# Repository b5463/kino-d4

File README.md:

<div align="center">
  <picture>
    <source media="(prefers-color-scheme: dark)" srcset="docs/assets/brand/kino-d4-white-on-dark.png">
    
  </picture>

  <h3>Four cameras. One button. One moving photograph.</h3>

  <p>

  </p>

  <p>
    <a href="#try-studio">Try Studio</a> ·
    <a href="docs/HARDWARE.md">Hardware</a> ·
    <a href="firmware-contract/README.md">Firmware contract</a> ·
    <a href="https://github.com/users/b5463/projects/3">Project</a> ·
    <a href="docs/DEVELOPMENT.md">Build notes</a> ·
    <a href="docs/VERSIONING.md">Versions</a>
  </p>
</div>

KINO D4 is a handmade four-lens camera built for house parties. Press the shutter and four cameras fire from slightly different positions. The result can stay as four photographs or become a short, looping wiggle with real parallax.

Direct flash. 4:3 frames. Originals saved first. No cloud anywhere near the shutter.

<p align="center"><sub>The actual Studio overview, connected to KINO Twin — the simulated camera that ships in this repository.</sub></p>

## Why this repository exists

A five-controller camera is miserable to service with an IDE, five serial logs, and hand-edited JSON. KINO Studio puts the whole machine behind one USB cable: all four sensors, power, storage, recipes, calibration, firmware, logs, and recovery.

The repository contains that workbench, the wire protocol it speaks, the Roll backend used after capture, shared document schemas, and a reference camera that can fail on command.

> **Honest build status.** The software works against the simulated camera and is covered by tests that need no hardware. That is Studio, the protocol, the Roll backend and its workers, the guest client, and KINO Twin.
>
> There is a real camera now. Firmware 0.4.55 captures on all four cameras and writes the originals to the card. It draws its own screens. Since 0.4.4 it has uploaded to a Roll over Wi-Fi from the body itself. The body is released too: design 0.1.4, a printable PETG slab, measured rather than estimated.
>
> Three things are not finished, and it is worth naming them here rather than leaving a reader to find out.
>
> The camera has **no flash**. [`ECN-0003`](hardware/changes/ECN-0003-shutter-on-jp1-21.md) dropped the assembly and gave its enable pin to the shutter. A replacement module has not been chosen.
>
> **Exposure skew between the four cameras has never been measured.** That is the number the wiggle's quality actually rests on. Firmware reports the two skews it can observe and returns `null` for this one, with a reason.
>
> **There is no public front door yet.** The operator's line sits behind O2 carrier NAT, so `kino.acronym.sk` cannot point at the PC, and no ingress has been selected — see [the standing decision](docs/runbooks/public-ingress-options.md#standing-decision-2026-09-09). A party still works: the camera writes to its card first and uploads when it can.

## Try Studio

You need Node.js 22 or newer.

```bash
npm ci
npm run build -w @kino/studio -w @kino/twin
npm run preview:all
```

Open <http://localhost:4400/studio/>, then open <http://localhost:4400/dev/twin/> in a second tab and press **CONNECT KINO TWIN** back in Studio. KINO Twin is the simulated camera: it speaks the same protocol as hardware, so Studio exercises its full interface without a D4 on the bench.

Both apps must be served from one origin, as `preview:all` does — the bridge between them is a `BroadcastChannel`. To run them on separate dev servers instead, start `npm run twin:relay` and open Twin with `?ws=1`; Studio offers the bridge automatically in a dev build.

A physical D4 needs desktop Chrome or Edge for Web Serial.

Run the checks:

```bash
npm run lint
npm run test -w @kino/studio -w @kino/kdp -w @kino/schemas -w @kino/test-fixtures -w @kino/hardware-profiles -w @kino/simulator-engine -w @kino/three-assets -w @kino/twin -w @kino/design-system -w @kino/media -w @kino/roll-web
npm run build
```

That is every JavaScript suite that runs without Docker, and the same line CI runs. The API and worker also need PostgreSQL, Redis, and S3-compatible storage; their local stack and ports are documented in [the development guide](docs/DEVELOPMENT.md#api-stack).

Two suites are outside that line on purpose. The firmware's are C, built and run with `make -C firmware/p4/host_tests test-all` and `make -C firmware/components/kdp_core/host_tests` — 6,246 checks that need no camera, and the two that link cJSON need the IDF container. KINO Print's are Python (`npm run test -w @kino/print`), so a bare `npm test` at the root fails on a machine without Python.

## The three tools

Every screen below is a capture of the running application against the included simulator. No hardware was attached.

### KINO Studio

The workbench behind one USB cable: all four sensors, power, storage, recipes, calibration, firmware, logs, and recovery. Shown at the top of this page connected to KINO Twin.

### KINO Twin

A working 3D copy of the D4. It speaks the same KDP as real hardware: power it on, fire the shutter, watch the display, click any part for its dimensions and clearances. Measurement findings gate the enclosure lock.

<p align="center"><sub>KINO Twin, simulator powered on. Everything shown is simulated and labelled as such.</sub></p>

### KINO Roll

The shared album after the party. The camera uploads over Wi-Fi; guests open a link, watch photos arrive live, view the four frames behind each one, favourite and download. The client is a PWA that works on a phone at the event.

The host gets a separate surface on the same link: a dashboard that says which camera is uploading and which is stuck, hides or restores a photograph, clears the roll, and exports the lot as a ZIP. A roll can carry a PIN, and a trashed photograph stays recoverable for seven days. There is a third surface for a screen at the party — a projector page that cycles the newest captures and keeps the display awake.

The Roll is run for an event rather than hosted permanently: the origin is a laptop, reached through an outbound tunnel for the night, with no port forwarded. [`docs/runbooks/event-day.md`](docs/runbooks/event-day.md) is the procedure, and it ends by taking the tunnel down.

<p align="center"><sub>The guest gallery with demo captures from the test uploader.</sub></p>

<p align="center"><sub>One photo: the D4 frame strip switches the preview. Simulated captures.</sub></p>

### And one workshop tool

[KINO Print](apps/prusa-print-98/README.md) is not part of the camera. It is a local print host for the MK3S that prints the body, and it is here because the bodies in this repository kept failing on the bed for reasons a slicer does not warn about. It reads the PrusaSlicer metadata out of a `.gcode`, refuses to start until a person confirms the printer is physically clear, and streams the job itself. Its PETG preflight is the point: it catches a first layer that is too hot, full-temperature probing, a profile mismatch, and a nozzle that heats before the bed wait, then holds the nozzle at 170 °C through bed heating and mesh levelling and raises it just before the prime line. The source file is never modified.

## What comes out of the camera

### WIGGLE

Four matched frames play `1 → 2 → 3 → 4 → 3 → 2`. Nothing is synthesized between them. The movement comes from the four real viewpoints.

### QUAD

Each camera can use a different recipe on the same shutter press. A single capture might produce PARTY NEG, MOTION, RAW DIGI, and ACROS-ISH together.

Both modes obey the same boring, important rule: the microSD card gets the originals before anything is rendered, uploaded, cropped, or shared. Derivatives are disposable. Originals are not.

## The camera

| Part | D4 V1 hardware |
|---|---|
| Main unit | Guition JC4880P443C-I-W, ESP32-P4 + ESP32-C6, 4.3-inch 480 × 800 touch display |
| Camera row | 4 × Seeed XIAO ESP32-S3 Sense |
| Sensors | 4 × OV3660 rolling-shutter sensors, up to 2048 × 1536 |
| Storage | 32 GB microSD |
| Battery | 1S 3000 mAh LiPo |
| Flash | **Not fitted.** `ECN-0003` dropped the direct-flash assembly and gave its enable pin to the shutter; an external module will replace it and is not chosen |
| Sound | 8 Ω / 2 W speaker |
| Camera wiring | Four UART pairs plus one shared sync line |
| Body | Printed PETG slab, 131 × 90 × 65.5 mm, design 0.1.4 — two-part chassis, glued face shell, sliding lens cover, dovetail rear door |

The boards are ordinary, replaceable parts. The exact power limits, wire gauges, battery constraints, mechanical stack, and confidence level of every measurement live in [`docs/HARDWARE.md`](docs/HARDWARE.md).

Two printable bodies are released, and they are alternatives rather than versions of each other. [`KINO_FIELD_BODY`](hardware/cad/KINO_FIELD_BODY/README.md) is the one above: PETG on a desktop printer, support-free, and its release is gated by 82 automated checks over the actual meshes — that every part prints flat, and that both print jobs fit a 250 × 210 bed. [`KINO_RESIN_BODY`](hardware/cad/KINO_RESIN_BODY/README.md) is printed entirely through JLCPCB in three parts, with an MJF nylon skeleton carrying everything and a clear SLA shell that touches nothing electrical, so it can be reprinted in another colour without re-qualifying an optical dimension.

The camera knows when its cover is shut without a switch. The Hall sensor the shell used to be drilled for had to be fitted before the face shell was glued on — the one irreversible step in the assembly — so it is gone. Closed, all four lenses face an opaque plate 0.2 mm away; firmware reads a mean luminance off the frames the viewfinder already decodes and decides from all four together. It ships observing only: the two thresholds have to be read at the bench, because the sensors run auto-exposure and a covered one reports amplified noise rather than zero.

### The screen on the camera

The camera runs its own interface on the 4.3-inch panel. No phone, no laptop, nothing to pair. A card for the thing you came to do, and five rows for everything else.

<p align="center"><sub>The home screen at 800 × 480. Drawn by the firmware's own code through <code>firmware/p4/host_preview</code> — not a photograph of the panel. The line at the top of the card is the worst condition: this render has two of its four camera stubs silent, the line says so, and the four-mark shows which two — a filled cell answers, an outline does not.</sub></p>

SHOOT is a card the full height of the panel, beside five rows a fifth of its height, because the camera is not a sibling of SETTINGS. The geometry says the hierarchy, so the screen needs no status strip at all — the card carries the worst condition when there is one and how many photographs are left when there is not. The card sits on the side of the hand that holds the body, so the thumb that rests there lands on it.

Type is Inter and Oxanium, rasterised to 8-bit coverage: Inter for everything a person reads as language, Oxanium for everything the camera says as a machine. Every corner, disc and chevron is drawn with per-pixel coverage rather than stamped from a bitmap, so no curve on the panel has a hard edge on it. The six menu marks are drawn too. The two brand marks, the KINO wordmark and the ODD JOBS symbol on ABOUT, are baked from the brand artwork to the same coverage by `tools/mkmask.mjs`.

Colour is one pink, and it means something happened. At rest the screen is ink on near-black, the same base as MAO, the studio's controller. The pink fills the SHOOT card, a control under a finger, and the four-mark for the 300 ms after a capture lands. Red is for a fault. The pink is not quite the same on every start: the camera takes one of eight shades from MAO pink a short way toward lavender, by its boot count, and wears it until it restarts. The palette, the eight shades and the rules for using them are in [`firmware/UI_DIRECTION.md`](firmware/UI_DIRECTION.md).

#### It starts by showing you the camera

The start opens on the maker's mark, ODD JOBS, in ink on black. Under it are four cells, one per camera, CAM1 top left, the way the four sit on the viewfinder and on the menu card.

<p align="center"><sub>Left: four cameras answering. Right: the same body with the third camera silent. Both are firmware renders.</sub></p>

**A cell fills when its camera answers**, not on a timer. A camera that has not answered after 1.6 s keeps an outline, drawn in full ink: a camera with a dead node says so on the first screen it shows, without a word of type.

**Then the four become the menu.** The cells turn dark while the box behind them turns this start's pink. The box grows into the SHOOT card, the cells into the card's four-mark, and the rows land beside it. That pink is the only colour in the start. With all four cameras up the menu is there in about two seconds, and in under three with one silent. A tap cuts the start short.

#### The rest of it

<p align="center"><sub>LOOK: the recipe in force, what it does at capture, and the three things you can change about it.</sub></p>

ROLL is the screen that matters at a party. It shows the QR a guest scans, the address for anyone who would rather type it, one word for the connection, and a count that comes from the card rather than from the server.

<p align="center"><sub>Also a firmware render. The roll name and code are invented for the render.</sub></p>

<p align="center"><sub>ABOUT: what this unit is, what each of the four cameras is running, and who made it.</sub></p>

All of these come out of a program that compiles `ui.c` and draws the screens on a workstation. It renders every screen for both hands, with the frames of every move, including every failure state — a card that will not mount, a server that has stopped answering, a capture that saved three frames out of four. Looking at the interface used to mean a build, a flash and a serial capture; now it is one command:

```bash
make -C firmware/p4/host_preview && firmware/p4/host_preview/preview out/
```

The same program is a gate, not just a viewer: it fails the run if any screen sets type outside the page margin, sets a word under its contrast floor, or leaves a touch target under 52 px. Clipping is the obvious fault, but the one an interface actually has is a sentence ending two pixels from the bezel — that does not look broken, it looks cheap, and it is much harder to catch by eye. It found four screens doing it the day it was written.

## One cable, five controllers

```mermaid
flowchart LR
    C1["CAM 1"] -->|"UART"| P4["ESP32-P4"]
    C2["CAM 2"] -->|"UART"| P4
    C3["CAM 3"] -->|"UART"| P4
    C4["CAM 4"] -->|"UART"| P4
    P4 --> SD["microSD originals"]
    P4 <-->|"KDP / USB"| Studio["KINO Studio"]
    P4 -->|"Wi-Fi after capture"| Roll["KINO Roll"]
    Twin["KINO Twin"] -.->|"the same KDP"| Studio
```

Feature code in Studio never reaches around the device API to poke a serial port. Real hardware, the test camera, and KINO Twin all go through the same framing, CRC checks, timeouts, commands, and capability negotiation.

That boundary matters. A simulator that gets special treatment is only a mockup. A simulator that speaks the real protocol can expose real bugs.

## The hard part is time

A shared GPIO edge does not make four rolling shutters expose at the same instant. KINO keeps three different measurements separate:

| Measurement | What it actually tells us |
|---|---|
| GPIO distribution skew | When each camera node handled the trigger |
| VSYNC phase skew | Where each sensor was in its rolling frame cycle |
| Effective exposure skew | When the scene was recorded |

A trigger spread under 100 µs can still hide 10 to 30 ms between real exposures. Studio reports the three values separately. If firmware cannot measure one of them, it returns `null` and says why.

## Repository map

| Path | Owns |
|---|---|
| [`firmware`](firmware/README.md) | What runs on the camera: the ESP32-P4 application, the four camera nodes, the C6 radio image, and the host test suites |
| [`apps/studio`](apps/studio) | Camera setup, shooting, looks, media, firmware, recovery, diagnostics |
| [`apps/api`](apps/api) | Rolls, authentication, uploads, object storage, live events |
| [`apps/worker`](apps/worker) | Derivative jobs, recaps, exports, trash purge |
| [`apps/roll-web`](apps/roll-web) | Public Roll guest PWA and private host dashboard |
| [`apps/twin`](apps/twin) | KINO Twin: 3D assembly, simulation, measurement, engineering exports |
| [`apps/prusa-print-98`](apps/prusa-print-98/README.md) | KINO Print: the local USB print host that prints the body, with the PETG preflight that stops a bad job |
| [`packages/kdp`](packages/kdp) | The KINO Device Protocol: frames, CRC, commands, transports, request lifecycle |
| [`packages/schemas`](packages/schemas) | Versioned `kino.*` documents shared across processes |
| [`packages/test-fixtures`](packages/test-fixtures) | Reference camera, recipes, media, and injected failures |
| [`packages/media`](packages/media) | Wiggle sequencing and playback, shared by the worker and the clients |
| [`packages/design-system`](packages/design-system) | The shared interface vocabulary |
| [`packages/hardware-profiles`](packages/hardware-profiles) | Board and sensor profiles the simulator and Studio read |
| [`packages/simulator-engine`](packages/simulator-engine) | The device simulation behind KINO Twin |
| [`packages/three-assets`](packages/three-assets) | Geometry and materials for the 3D twin |
| [`firmware-contract`](firmware-contract) | The contract camera firmware must implement, and every recorded deviation from it |
| [`hardware`](hardware) | BOM, wiring, assembly, acceptance tests, two released printable bodies, and the Rev1 mainboard schematic |
| [`infra`](infra/README.md) | Compose files, the deploy script, backups, and the load and latency harnesses |
| [`kino_dev_spec_pack`](kino_dev_spec_pack) | Permanent Studio and Roll product specifications |
| [`kino_twin_spec`](kino_twin_spec) | The 3D twin and virtual-device specification |

## Read the right thing

This project has history, and some old planning material is still useful. It is not always current. Start with [`docs/README.md`](docs/README.md), which says which source wins when code and prose disagree.

- [Hardware reference](docs/HARDWARE.md): parts, dimensions, power, wiring, and what still needs measuring
- [Architecture](docs/ARCHITECTURE.md): process boundaries, state ownership, uploads, and package relationships
- [Development](docs/DEVELOPMENT.md): setup, services, migrations, tests, and protocol changes
- [Troubleshooting](docs/TROUBLESHOOTING.md): browser, USB, protocol, power, sync, media, recovery, and API failures
- [Firmware contract](firmware-contract/README.md): the handoff extracted from working protocol source, and every deviation the firmware is allowed
- [Firmware](firmware/README.md): what runs on the camera, how to build all three configurations, and what each host suite covers
- [Hardware build package](hardware/README.md): BOM, wiring, assembly order, and acceptance sheet
- [Field body](hardware/cad/KINO_FIELD_BODY/README.md) and [resin body](hardware/cad/KINO_RESIN_BODY/README.md): the two printable bodies, their measured inputs, and the gates each release passes
- [Running an event](docs/runbooks/event-day.md): the whole night, from bringing the stack up to taking the tunnel down
- [Restoring from backup](docs/runbooks/restore.md) and [what to watch](docs/runbooks/observability.md): the two things needed when a party is already underway
- [Host guide](docs/roll/HOST_GUIDE.md): the Roll dashboard, written for whoever is running the camera rather than for a developer
- [Contributing](CONTRIBUTING.md): required contracts, tests, measurements, and pull request rules
- [Roadmap](ROADMAP.md): current work and the deliberately unfinished edges
- [Releasing](docs/RELEASING.md): independent versions, compatibility review, artifacts, and publishing
- [Versioning](docs/VERSIONING.md): software, protocol, schema, database, and hardware revision rules
- [Security](SECURITY.md): private reporting and the high-risk surfaces
- [Brand assets](docs/assets/brand/README.md): the four split D4 marks and where each belongs
- [Product media](docs/assets/product/README.md): real and simulated asset rules plus the physical shot list

The short version: tested protocol source beats old prose, unknown hardware measurements stay unknown, originals are immutable, and firmware changes are finished only when the contract and tests move with them.

## License

KINO software and general documentation use the [MIT License](LICENSES/MIT.txt). Physical design source uses [CERN-OHL-S-2.0](LICENSES/CERN-OHL-S-2.0.txt), which keeps distributed hardware modifications open. Logos, wordmarks, product media, and the unaudited recovery archive remain reserved.

[`LICENSE`](LICENSE) explains the boundary, [`REUSE.toml`](REUSE.toml) records it for SPDX tooling, and [`TRADEMARKS.md`](TRADEMARKS.md) keeps compatible forks distinct from official KINO releases.

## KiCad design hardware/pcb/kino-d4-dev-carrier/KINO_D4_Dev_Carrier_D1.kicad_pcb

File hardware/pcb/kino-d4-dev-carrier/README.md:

# KINO D4 dev carrier D1

A bench carrier for the four XIAO ESP32-S3 Sense camera nodes on the Guition P4. It carries exactly what the firmware drives today (`firmware/p4/main/board_d4v1.h`) and nothing from the A0.2 feature set: no charger, gauge, PD sink, haptics, IMU, RTC, current monitor or power controller. Those come back one at a time, as breakouts on the Qwiic port first, when their firmware exists.

Why it exists: the A0.2 quote was about 500 EUR for two assembled boards and 600 EUR for five. Roughly 430 EUR of that was fixed cost (double-sided assembly, 42 BOM lines without an LCSC number, extended-part fees). D1 is 2 layers, SMT on one face, 19 BOM lines of which 13 are JLC basic parts. Tracking: [issue #250](https://github.com/b5463/kino-d4/issues/250), [ECN-0008](../../changes/ECN-0008-dev-carrier-d1.md).

Status: design package 0.1.9, DRC 0, ERC 0, 0 unconnected, fab package in `outputs/fab-d1/`. Not yet ordered. Order after the [checks before ordering](#checks-before-ordering).

## What is on it

| Block | Parts | Notes |
|---|---|---|
| Outline and mounting | 117.01 x 69.41 mm, four 2.2 mm NPTH for M2 | A0.2's outline and the P4 inner-insert pattern (61.9 x 54.8 mm, offset -9.3 mm). Holes H1-H4 at the coordinates in `kino-d4-carrier-a0/MECHANICAL.md`. 7 mm fastener allowance kept clear. |
| P4 ribbon | J100, 2x13 keyed box header, top face | 1:1 to P4 JP1 over a ribbon that leaves over the left board edge and folds down to JP1 beneath. The fold rotates the far socket about the edge and swaps the two columns in the board frame, so J100's pin 1 sits at JP1's even-column x (6.0 mm) with the rows unchanged; the shroud key follows. Pin 15 (GPIO35, the boot strap) is open and marked NC on the back. Pin 1 against the real ribbon is the first check before ordering. |
| Camera sockets | J200-J500, two 1x07 sockets each, 22 mm pitch | Same centres as A0.2. Only D1 (sync), D6 (TX), D7 (RX), 3V3, GND and 5V are wired. |
| Camera power | U200-U500 TPS2553, 24k ILIM | One switch per node, 1.0-1.2 A limit, all four enabled by CAM_PWR_EN (GPIO31, JP1 pin 10). R100 (4.7k) holds the bank off until firmware drives the pin, and still off against the P4's 45k internal pull-up if firmware ever enables it. The four FAULT_N open drains share one net. In current limit a switch does not open: it holds its limit (about 1 V across a 1 ohm short), asserts FAULT after 7.5 ms and thermal-cycles until the short clears. An LM66100 ideal diode (U201-U501, CE on VOUT) sits between each switch and its link header: about 0.1 V at the 1.2 A limit, and a node's own USB can never feed the bank. |
| Indicators | D1000 PWR (5 V in, green), D1001 CAM (bank enabled, green, from GPIO31 through 470 ohm), D1002 FLT (any channel in fault, red; its 1k is the FAULT_N pull-up) | Board status only, no per-node LEDs. Bottom face, bottom edge left of the USB-C, so they show through the spacer gap with the carrier on the P4. Named on both faces. |
| Link headers | JP200-JP500, 1x02 + shunt, top face | Pull the shunt before plugging a node's USB; refit after. |
| Signals | 2.2k series on every P4-to-node and node-to-P4 line and on the four sync lines | Stops a powered P4 pin feeding an unpowered node through its protection diodes. No isolation buffers. |
| 5 V input | J1000 USB-C, U1000 USBLC6-2SC6, F1000 3 A PPTC, 5.1k on CC1/CC2, 2 x 22 uF, D1003 SMAJ5.0A on the rail | 5 V at up to 3 A from a Type-C source. No PD. U1000 clamps VBUS and both CC pins. F1000 (1812 polyfuse, hand-fit: the JLC polyfuses are extended-library parts) protects the board and the source if the rail shorts. |
| Power module | J1001 JST XH 2.5 mm 6-way, keyed: `VBUS VBUS GND GND RAIL RAIL`; JP1001 solder bridge, closed as shipped | Two 3 A contacts per rail, 20 AWG to the module. The fused USB VBUS leaves on 1-2 to the SW6106 charger/boost input, so the battery charges from the carrier's USB-C; the 5 V rail comes back on 5-6 from the SW6106 output and feeds the cameras and, through U1001, the P4. JP1001 closed: no module, USB is the rail (bench). Open JP1001 when the module is wired, or USB back-feeds the boost output. U1002 (LM74700-Q1) with Q1000 (IRLML0030, 20 V gate: the controller drives the gate up to 13.9 V) is an ideal diode in the VBUS path toward J1001, with 1 uF on its anode and cathode. With JP1001 open, a charger on the module's own input port cannot back-drive the carrier's USB-C (20 mV forward, off at -11 mV, 5.3 A FET); with JP1001 closed the rail node bypasses U1002, which is why the bridge is opened the moment a module is wired. One rule the copper does not enforce remains: the rail must come from a 5 V-only output with no PD or QC sink on the same node, because 9 V kills every IC on the rail. D1003 (SMAJ5.0A at J1001) clamps transients, not a sustained 9 V, and its 6.4 V breakdown sits above the LM66100's 6 V and the TPS2553's 7 V absolute maximum: no clamp fits under 6 V on a 5.25 V rail, so the ideal diodes rely on the SW6106's own regulation for anything slower than a transient. |
| P4 supply | U1001 LM66100 ideal diode, 1 uF either side | Rail to the P4's 5 V pins (JP1 2/4, two ribbon conductors, about 1 A each). CE tied to VOUT: the rail feeds the P4; the moment the P4's own USB lifts its side 35 mV above the rail the switch opens, so the P4 USB can never feed the rail or the cameras, and with both present the higher source carries the P4 with no current between them. 79 mOhm, about 0.1 V drop at 1 A; 1.5 A continuous, enough for the module alone. |
| Current-measure links | R206/R306/R406/R506, 0 ohm 0603 | In each node's 5 V between the link header and the socket. The easy way to read a node's current is an ammeter across its LINK header with the shunt out; the 0 ohm link is the soldered alternative (lift it, meter TPn05 to TPn04) when the header is in use. |
| Qwiic pull-ups | R102/R103, 4.7k 0603, DNP | Pads only. The P4 bus has the touch controller's pull-ups; fit these for a breakout that brings none. |
| Fiducials | FID1-FID3, 1 mm copper, 2 mm mask, bottom face | For the assembler's placement. |
| Scope grounds | GL1-GL3, wire loops, hand-fit | GND at the controls, at the power block and right of CAM 4. |
| Shutter | J103 JST XH 2-way socket for the shutter button's two-wire lead (dry contact) | Pulls SHUTTER_N (GPIO28, JP1 pin 21) to GND; the internal pull-up and the 25 ms debounce in `buttons.c` do the rest. Keyed, and either way round works since it is a contact to GND. No button on the board. |
| Service | J101 1x06: GND, C6 3V3 (sense only), RX, TX, IO9, EN | The C6 lines from JP1 pins 18-26. |
| Expansion | J102 JST SH 1x04, Qwiic/STEMMA QT pinout | P4 I2C (JP1 pins 23/25) at 3.3 V. The bus already carries the touch controller at 0x5D. |
| Test pads | TP100-TP107, TP200-TP505, 1.5 mm, bottom; TP110-TP117, 1.5 mm, top | Bottom: P4 3V3, 5V, SYNC, CAM_PWR_EN, SHUTTER, GND, FAULT_N; per camera TX, RX, SYNC, 3V3, 5V, 5VJ. Top, reachable with the carrier mounted: 3V3, 5V, SYNC, EN, SHUTTER, GND, FAULT, RAIL in one row under the GPIO map. Named on the silk. |

Battery operation: LiPo -> F3A -> 1S protection -> SW6106 -> J1001 RAIL -> 5 V bus -> four TPS2553 (1.2 A each) and the P4 over U1001. What protects what: the pouch fuse and the BMS cover the pack; the SW6106 limits its output (18 W class, about 3 A) and is the only charger; F1000 covers the USB input; each node has its own current limit and fault flag, so one shorted camera drops that channel, not the rail; the SS34s keep a node's USB off the bank. The rail itself has no fuse of its own on the carrier: the SW6106 limit is it. Current budget: the 1.0 mm 5 V bus on 1 oz copper carries about 3 A for a 10 degC rise. Four XIAO S3 Sense modules with cameras draw about 2 A together; flash is not on this board. Bulk capacitance is 2 x 22 uF at the input and 22 uF per node; if PWR flickers or a node resets under a camera-plus-WiFi burst, add 100 uF or more across TP101 (5V) and TP105 (GND) before changing anything else.

## Pre-build analysis

`design/verify.py` runs the checks a board can pass before it exists and writes [`outputs/VERIFY-D1.md`](outputs/VERIFY-D1.md): every net reaches two pads; the polarity of every diode, LED and IC and the function of every protection part against the intent; J100 against the measured JP1 table in `board_d4v1.h`, pin by pin; the XIAO socket pins; every power net at its class width end to end, with copper length and resistance; nothing but silk inside the 7 mm fastener allowance; every LCSC number present, in the recorded library class, in stock; the fab package against the board. Run it after `release.py`; it exits 1 on any failure. DRC, ERC and the unconnected count come from `release.py`.

The numbers below are estimates from datasheets and the routed copper. Nothing on this board has been measured; `firmware/HARDWARE_VALIDATION.md` records the current draw as unmeasured. Each line says what it assumes.

### Voltage at the loads

Rail 5.00 V at J1001. Copper from `VERIFY-D1.md`, 1 oz.

| Path | Drops | At the load |
|---|---|---|
| Node at 0.5 A (camera on, radio off) | bus copper up to 0.15 V at 3 A total on the far channel; TPS2553 90 mohm 0.05 V; LM66100 79 mohm 0.04 V; link and socket copper 0.1 ohm 0.05 V | about 4.7 V at the XIAO 5 V pin |
| Node at 1.0 A (radio burst) | LM66100 0.08 V, TPS 0.09 V, copper 0.1 V, bus 0.15 V | about 4.6 V |
| P4 at 1.0 A | LM66100 79 mohm 0.08 V; copper 34 mohm 0.03 V; two 28 AWG ribbon conductors over 100 mm about 0.01 V | about 4.87 V at JP1 |
| Bench, USB is the rail | PPTC about 50 mohm 0.15 V at 3 A; VBUS and bridge copper 40 mohm 0.1 V | rail about 4.75 V at 3 A, add the node drops above |

The XIAO's 3.3 V regulator holds to about 3.6 V in, so 4.6 V is a full volt of margin. The largest drop left is the bus copper at full load.

### Dissipation at full load

TPS2553 at its 1.2 A limit 0.13 W (SOT-23-6, about 200 K/W, +26 K); LM66100 at 1.2 A 0.11 W (SC-70, about 250 K/W, +28 K); the P4's LM66100 at 1 A 0.08 W; Q1000 at a 3 A charge 0.24 W (27 mohm; SOT-23, the warmest part on the board, +30 K at the datasheet 125 K/W; 0.1 W at a 2 A charge); the 1.0 mm bus at 3 A about 10 K over ambient. The PPTC holds 3 A at 25 degC and about 2.4 A at 50 degC: with the stack shooting while the battery charges, the input can reach 3 A, so set the SW6106 input limit to 2 A or expect the fuse to open after minutes in a hot enclosure.

### Battery run time

11.1 Wh pack (3000 mAh, 3.7 V), 90 % usable to the BMS cut-off, 88 % boost efficiency: 8.8 Wh at the rail. Loads assumed: P4 module 1.6 W (Guition's 320 mA figure); XIAO S3 Sense 0.4 W idle with the camera off, 1.25 W streaming or capturing.

| Mode | Load | Run time |
|---|---:|---:|
| Ready, four nodes idle | 3.2 W | about 2.7 h |
| One capture a minute (5 s active) | 3.5 W | about 2.5 h |
| Continuous preview or shooting | 6.6 W | about 1.3 h |

### Charging through the carrier USB-C

A 5 V 3 A source on J1000 minus the stack: idle leaves about 2.3 A for the SW6106 input, so the 3000 mAh pack reaches 80 % in about 1.7 h and full in about 2.5 h; shooting while charging leaves about 1 A and roughly 4 h. The SW6106 passes input power through, so the stack runs during the charge. The PPTC hold current is the ceiling on charge plus load.

### Data and shot timing

From the firmware and the Twin choreography: a 400 KB JPEG per node moves in about 4.4 s at 921600 baud, all four channels at once on separate UARTs, so a four-camera shot clears in about 5 s including capture; at 3 Mbaud (the ladder in #228, adopted only after LINK_BENCH proves it on the harness) about 1.5 s. The 2.2k series resistors into about 20 pF of pin and track give a 44 ns time constant, a 10-90 % edge of about 100 ns: 9 % of a bit at 921600, 30 % at 3 Mbaud. Fine at 921600; at 3 Mbaud the eye is still open but the margin is thin, which is one more reason the ladder is bench-gated. Sync phases are tens of microseconds to milliseconds; the carrier adds no delay the P4 does not already own.

### Stack, cable and fit

- Faces: every SMT part faces the P4; J100, the XIAOs, link headers, controls and J1001 face up.
- Spacer height: only the P4-side plug is in the gap: JP1's 2.54 mm header plus IDC socket and strain relief, 11-14 mm (the P4's header height is not recorded in MECHANICAL.md; measure it). 15 mm M2 standoffs if that measures under 14 mm, 20 mm otherwise. The USB-C plug overmold (6.5 mm) and the Qwiic cable fit either way. On the top face the J100 stack (9.1 mm shroud plus plug, about 15 mm) stands beside the XIAO stack of the same height.
- Ribbon: 26-way 1.27 mm (33 mm wide), about 8 mm from J100 to the left edge, down the gap, 8 mm back to JP1, plus the two sockets: 60 mm with 15 mm standoffs, 70 mm with 20 mm. Pin 1 stripe to the chamfer on J100 and to pin 1 on JP1; the key on J100 stops a reversed plug. Power everything down before touching the ribbon: an IDC plug is not ground-first.
- Power module: 20 AWG from J1001 (two contacts per rail) to the SW6106 pads; keep it under 150 mm so the rail drop stays under 0.05 V at 3 A.
- Nodes: XIAO on 8.5 mm sockets, the Sense camera board on top, about 15 mm above the carrier plus the lens. 22 mm pitch leaves 4.5 mm between modules for the camera flex.
- Outline: 117.01 x 69.41 mm, the P4 module envelope recorded as `CONFLICT` in `docs/HARDWARE.md` (an alternate 114.4 x 66.8 mm figure exists), which is why the 1:1 template check comes before ordering.

## Flashing and test

- Nodes: pull that channel's LINK shunt, plug the XIAO's own USB-C, flash, unplug, refit the shunt. The ideal diode keeps the node's USB off the bank either way; the shunt keeps the bank off the node's USB and the PC port. The LINK headers sit in the gap between sockets (x = node centre + 11 mm), outside the 12.4 mm plug overmold, so the plug goes in with the node seated.
- P4: its own USB-C, as without the carrier, at any time: U1001 keeps the two 5 V sources apart.
- C6: J101 (GND, 3V3 sense, RX, TX, IO9, EN) carries the C6 lines from JP1 pins 18-26.
- Test: every firmware GPIO has a pad (TP100-TP107), every node has TX/RX/SYNC/3V3/5V/5VJ pads and a 0 ohm current link, GL1-GL3 are scope grounds, FAULT_N is on TP107. The node pads face the P4; the P4 signals, the rail and FAULT are repeated on the top face (TP110-TP117) so the carrier can be probed while mounted.
- The SW6106 class of module switches off at light load after some tens of seconds. With the P4 unplugged and the nodes idle the rail may drop; bring-up step 7 may need the module's key.

## Legend

Drawn by `design/silk.py`. Arial Bold throughout (an outline face every KiCad install resolves; the file is patched after save because the Python API has no font setter), nothing under 1.0 mm, every legend piece a separate silk item so DRC checks the gaps. Every item is a designator, a pin, a limit, a procedure or an identity field.

The top of the hierarchy (`KINO D4`, `SIDE A/B`, `CAM 1-4`, `PROTOTYPE`, `5V IN`) is reversed out of solid silk blocks (KiCad knockout text); nothing else is boxed. Type scale, three sizes only: 3.2 mm for the board name and the side marker, 1.8 mm for section names (`DEV CARRIER`, `REV D1`, `PROTOTYPE`, `CAM n`, `5V IN`, the column headers), 1.0 mm for every label, designator, pin and note. Layout: one left margin (x 3.6) and one right margin (x 114) for the top band, the identity line and the power block; the identity line on one baseline, two sizes (name 2.4, the rest of the group 1.4), part number and date 1.0 right-aligned; text is left-aligned on its block's margin or centred on the part it names, never mixed in one block; every bottom-row label on one baseline (y 64.6).

Front ("SIDE A"), the face the XIAOs stand on: the ODD JOBS mark top left; between the inserts the subtitle `4x XIAO ESP32-S3 SENSE ON ESP32-P4 JP1` with the two bench facts under it (`LINK: PULL THE SHUNT BEFORE NODE USB`, `CAM 5V: 1.2A LIMIT PER NODE, SHARED ENABLE`); `SIDE A`; the identity line `KINO D4 / DEV CARRIER / REV D1 / PROTOTYPE ... KINO-D4-DC-D1 / 2026-11` (the prototype marking is on both faces); per node `CAM n`, `Jn00`, `LINK` over the header in the gap to the right, `XIAO ESP32-S3`, pin 1 and the six wired socket pins named inside the rows (visible when the module is out); `J1001 POWER` with `VBUS GND RAIL` beside the connector in the column right of CAM 4; `J100 P4 JP1` beside the ribbon shroud (its chamfer is pin 1); the GPIO map under it (`CAM EN GPIO31`, `SYNC GPIO32`, `SHUTTER GPIO28`); `J103 SHUTTER` (the JST XH socket for the shutter lead, `SW GND`) and `J101 C6 SERVICE` with their pins named, on one axis; `5V IN` over `J1000 USB-C 3A MAX` against the right margin; `PWR CAM FLT` over the edge LEDs; the top-face pad row `3V3 5V SYNC EN SHUT GND FLT RAIL` under the GPIO map.

Back ("SIDE B"), the assembled face and the one the engineer probes with the carrier off the P4, laid out in the same reading order and on the same margins as the front: the top strip holds the S/N box on the left margin, the `JLCJLCJLCJLC` anchor, and the record as one block (`ODD JOBS`, `CERN-OHL-S-2.0`, the repository URL); `SIDE B` and the identity line; `J100 P4 JP1`, `1` and `NC` (pin 15) at the header pins, which come through from the top face, and `U1001 RAIL > P4 5V` at the ideal diode; `CAM 1-4` as reversed tags over each switch block with every test pad named (`5VJ 5V 3V3 SY RX TX`); the P4 pads `EN 3V3 5V SY SH` and `GND`; the power corner read in the order the current flows (`USB-C IN > U1000 ESD > F1000 3A > JP1001 RAIL > U1002 J1001`) with `D1003 TVS`, `F1000`, `JP1001`, `J1000`, and the J1001 contacts `VBUS GND RAIL` named where the pins come through; `GND` and `FAULT` at the pads, `FLT CAM PWR` at the LEDs; `J102 QWIIC GND 3V3 SDA SCL` and `PU DNP`. On the front `GND` marks the three wire loops.

## Files

| File | Content |
|---|---|
| `design/circuit.py` | Every part, net and pin, with the LCSC number and JLC library class checked on 2026-11-05 |
| `design/placement.py` | Outline, holes, camera centres, every part position and face |
| `design/build.py` | Writes the schematic (`*.kicad_sch`, `KINO_DEV.kicad_sym`), footprint library, project file and placed board |
| `design/route.py` | `export` writes the DSN with the power classes; `import` reads the Freerouting session, fixes the USB-C stubs, pours GND on both faces |
| `design/silk.py` | The legend on both faces |
| `design/release.py` | Gerbers, drill, BOM, CPL, hand-fit list, DRC/ERC reports, `outputs/BUILD_STATUS.json` |
| `design/verify.py` | The pre-build checks: nets, polarity and intent, pin maps against the firmware, power copper, keep-outs, JLC parts, fab package; writes `outputs/VERIFY-D1.md` |
| `design/print3d.py` | `outputs/D1-print.stl`: the board body from KiCad (outline, holes) and every component as a box at its datasheet envelope, SMD parts included, on both faces. The J100 shroud is hollow with its key notch so a real IDC socket drops in. No pins, no mated plugs, no XIAO modules. For a clearance print against the P4. |
| `KINO_D4_Dev_Carrier_D1.kicad_pcb` | The routed board |
| `outputs/fab-d1/` | The order package |
| `KINO_DEV.pretty/` | The XIAO socket and USB-C lands, copied from `kino-d4-carrier-a0/KINO_A0.pretty/` |

Rebuild from scratch, with KiCad 10's bundled `python.exe` and the Freerouting jar:

```
python design/build.py
python design/route.py export WORK
java -jar freerouting.jar -de WORK/d1.dsn -do WORK/d1.ses -mp 80 -mt 4 -l en
python design/route.py import WORK
python design/silk.py
python design/release.py
python design/verify.py
kicad-cli pcb export stl --board-only -o outputs/D1-3d-base.stl KINO_D4_Dev_Carrier_D1.kicad_pcb
python design/print3d.py
```

The ODD JOBS symbol is read from `kino-d4-carrier-a0/brand/odd-jobs-symbol.json` at build time; it is not copied into this directory.

## Ordering

JLCPCB, 2 layers, 1.6 mm, 1 oz, any finish. Economic assembly, bottom side only (set the assembly side to Bottom on the order form); the placement count is in `outputs/BUILD_STATUS.json`. Upload `outputs/fab-d1/` as the Gerber zip, `BOM-D1-JLC.csv` and `CPL-D1-JLC.csv`. The CPL carries KiCad's angles and JLC re-maps them per footprint, so check every polarised part in the assembler's preview before confirming: U200-U500, U1000 and U1002 (SOT-23-6 pin 1), U201-U501 and U1001 (SC-70 pin 1), Q1000 (SOT-23, source on the fused VBUS side), D1003 (SMA cathode bar), D1000-D1002 (LED cathode), J102 pin 1, J1000. Expect a note from JLC about the stock-footprint 0.12 mm silk outlines (under their 0.15 mm minimum; cosmetic) and about U1000 and J102 within 1.1 mm of the edge (they add rails for Economic). Hand-fit the parts in `BOM-D1-HANDFIT.csv` after delivery: eight 1x07 sockets, the box header, the C6 header, four 1x02 link headers with shunts, the 1812 polyfuse, the JST XH power connector (6-way) and shutter socket (2-way), three wire loops.

## Checks before ordering

- [ ] Print the 1:1 mounting template from `kino-d4-carrier-a0/outputs/` and lay it on the P4: the inner-insert offset is drawing-derived (MECHANICAL.md).
- [ ] Print `outputs/D1-print.stl` (1:1, front face up, 0.2 mm layers, PLA; every part is a box on the 1.5 mm plate, so nothing above the board needs support. The USB-C, Qwiic and SMD envelopes hang below the board: print on tree supports under the board, or slice the model 3.5 mm up on supports) and stand it on the P4 on the intended standoffs: your IDC socket into the hollow J100 shroud and the ribbon fold over the left edge, a USB-C plug under the board, a XIAO on its sockets with its USB-C plug beside the LINK header, the JST leads at J1001 and J103. Body sizes are datasheet envelopes, not measured.
- [ ] Pin 1: with the real ribbon folded over the left edge, socket A on J100 and socket B on JP1, the stripe must land on JP1 pin 1. J100 pin 1 is placed at JP1's even-column x on the reasoning that the fold swaps the columns; if the stripe lands on pin 2 instead, rotate J100 180 degrees in `placement.py` (pin 1 to x 8.54) before ordering.
- [ ] Spacer height: measure the P4's JP1 header plus a mated IDC socket with strain relief; 15 mm standoffs under 14 mm, otherwise 20 mm.
- [ ] XIAO USB-C plug clears the LINK header and the neighbouring module with a node seated (plug overmold about 12.4 x 6.5 mm).

## Bring-up

1. No XIAOs, no P4: 5 V in on J1000. PWR on, CAM and FLT off. CAM_PWR_EN low: all camera 5 V pads 0 V.
2. P4 on the ribbon, firmware up: `CAM_PWR_EN` high, CAM on, each CAMn_5V pad at 5 V.
3. One XIAO at a time in each socket: the node answers on its UART (issue #148's single-node proof).
4. Four nodes: all visible at once; SYNC on every TP*02 pad.
5. Short a camera 5 V pad to GND through 1 ohm: the switch holds about 1.1 A, so the pad reads about 1 V, FLT comes on and TP107 goes low after about 8 ms, the SOT-23 warms and thermal-cycles; the other three nodes still answer. Remove the short: the channel recovers on its own.
6. Node current: pull JP200's shunt and put an ammeter across its two pins: node 1 idle, streaming, and with the flash command. Refit the shunt. (Soldered alternative: lift R206, meter TP205 to TP204.)
7. Charging path: open JP1001, wire J1001 1-2/3-4 to the SW6106 input and 5-6/3-4 from its output. USB-C on the carrier: the SW6106 charge LED on, the rail at 5 V, the P4 up. Pull the USB: the stack keeps running from the battery. Plug the P4's own USB with the rail live: TP101 (P4 5V) rises to the USB level, the rail does not move, no current on the RAIL pair.
8. Measure whether JP1 pin 2 is tied to the Guition module's own USB VBUS (meter, module USB unplugged, carrier powered). If it is, the module's onboard battery connector also charges from the carrier; if there is a diode drop, it does not, and the SW6106 path is the only charger. Record the result in `docs/HARDWARE.md`.

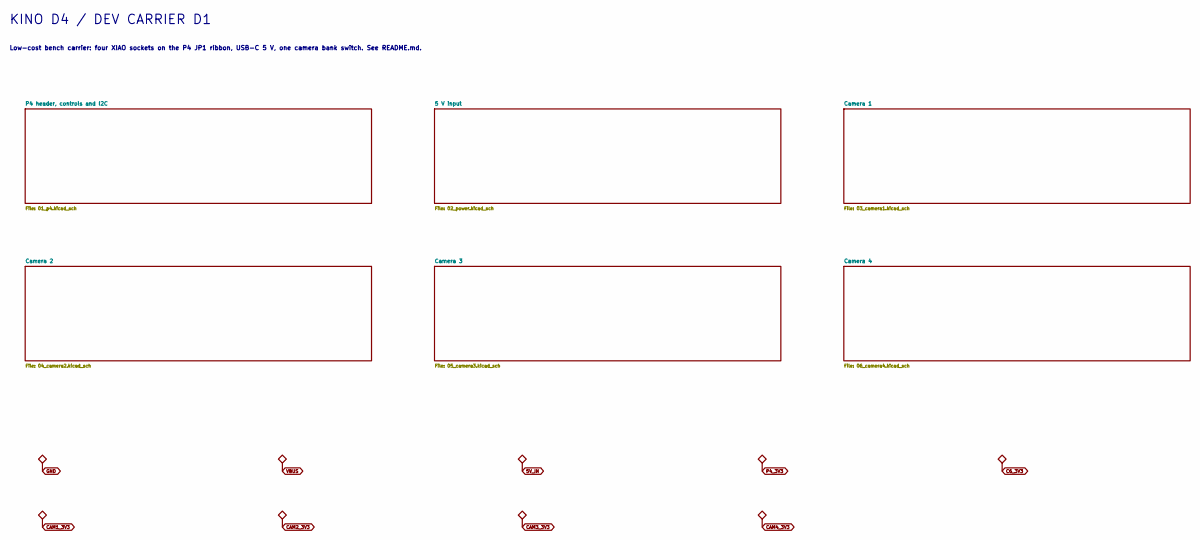
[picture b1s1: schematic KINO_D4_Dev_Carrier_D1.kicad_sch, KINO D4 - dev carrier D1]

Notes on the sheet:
KINO D4 / DEV CARRIER D1
Low-cost bench carrier: four XIAO sockets on the P4 JP1 ribbon, USB-C 5 V, one camera bank switch. See README.md.

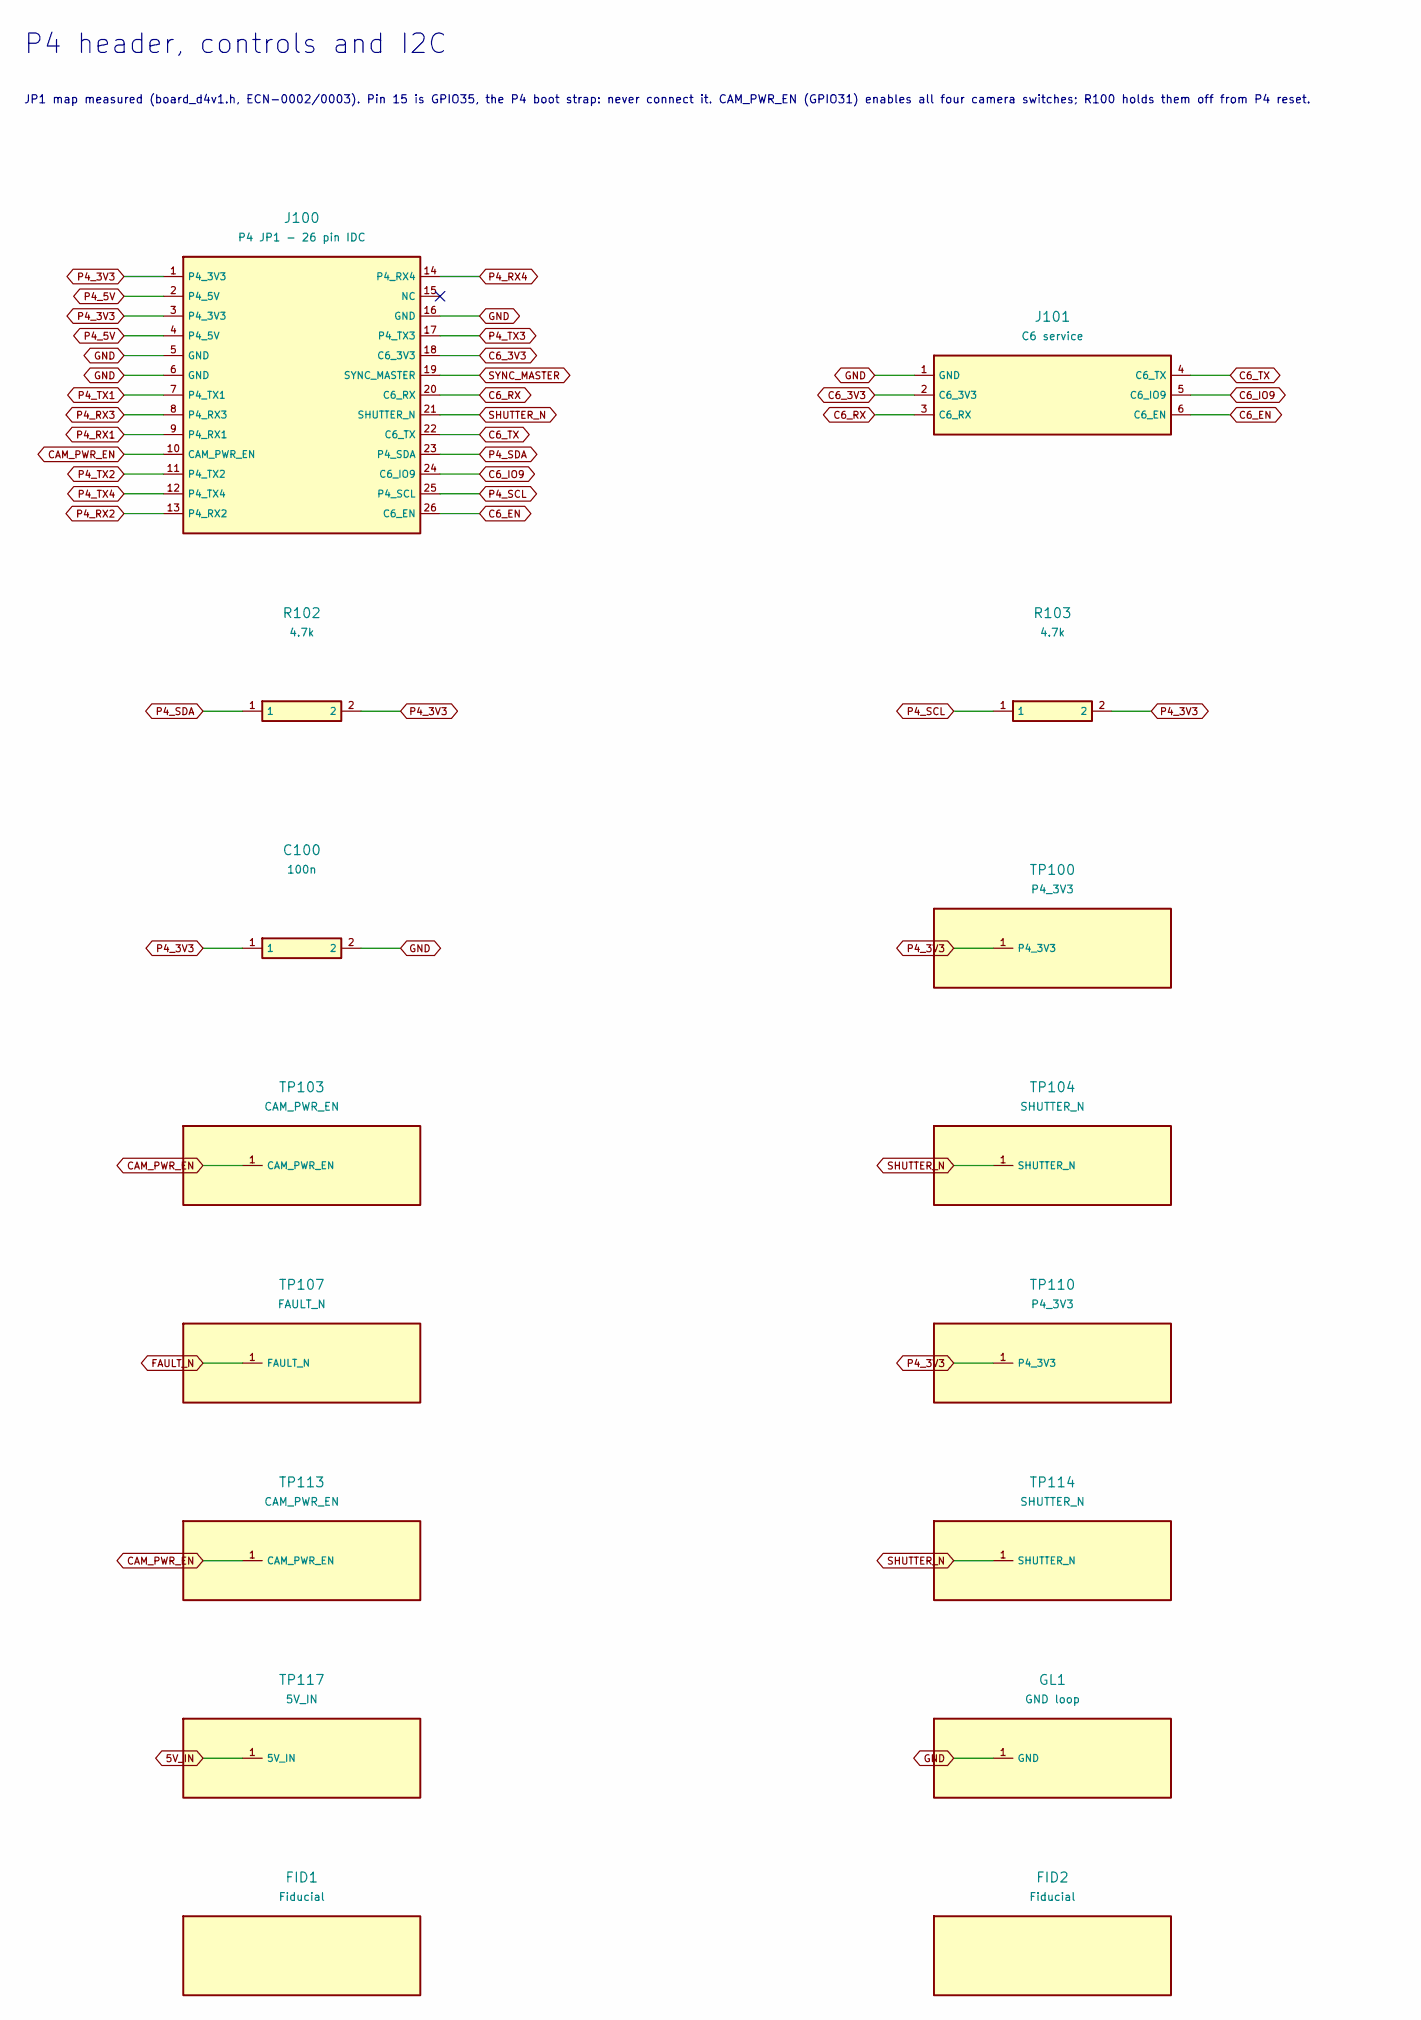
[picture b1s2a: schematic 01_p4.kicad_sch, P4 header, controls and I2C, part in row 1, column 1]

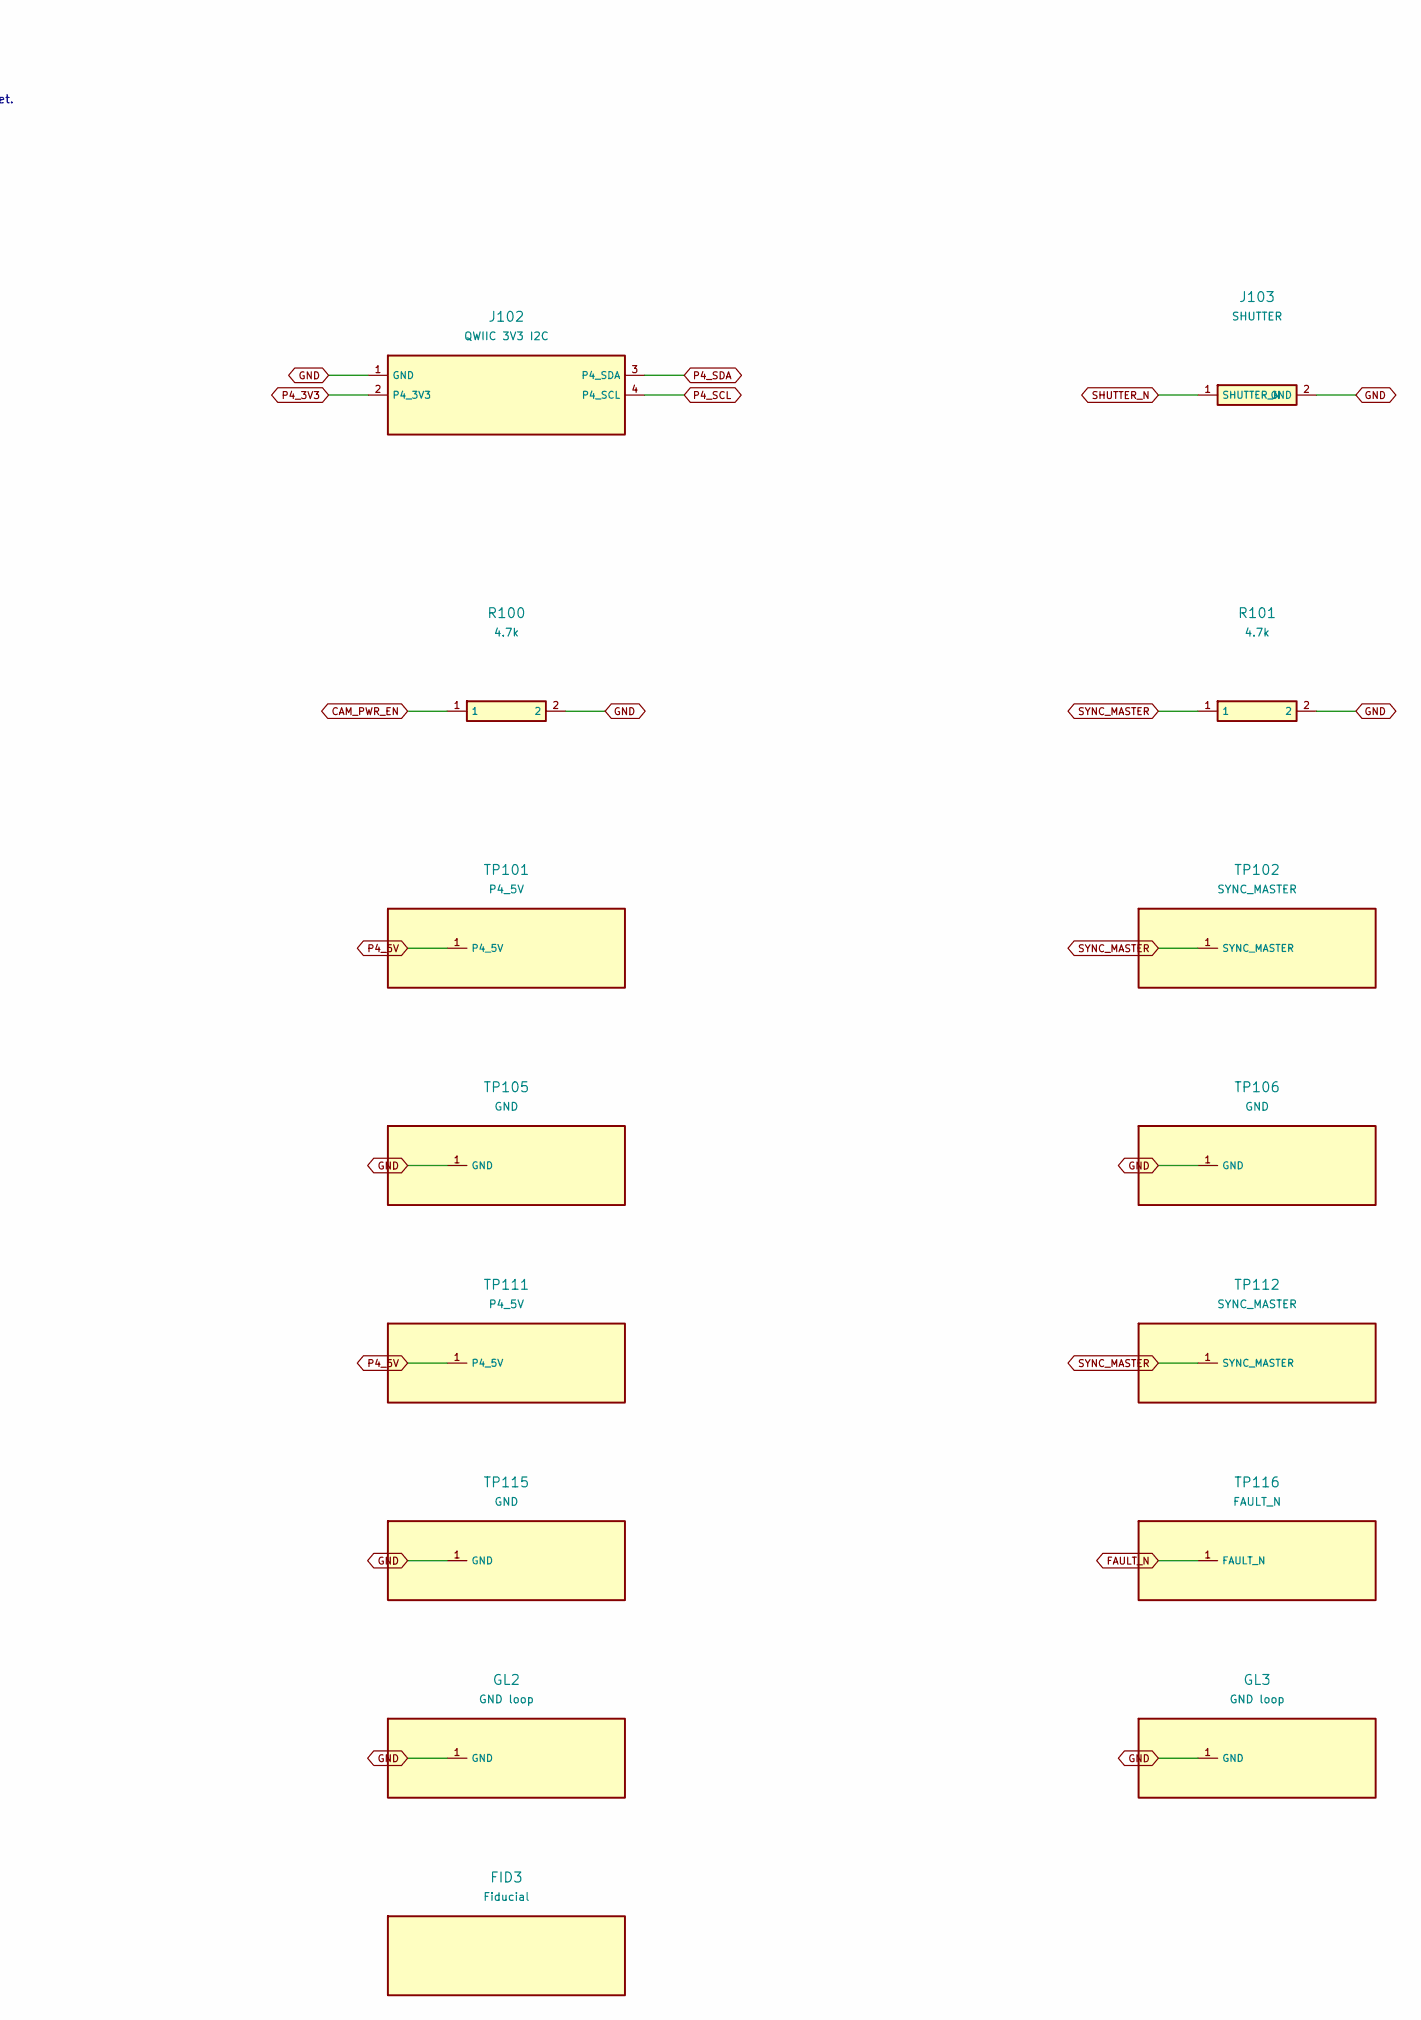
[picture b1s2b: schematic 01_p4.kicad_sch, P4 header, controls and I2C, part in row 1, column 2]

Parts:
C100: 100n; C_0603_1608Metric; LCSC C14663
FID1, FID2, FID3: Fiducial; Fiducial_1mm_Mask2mm
GL1, GL2, GL3: GND loop; TestPoint_Loop_D2.50mm_Drill1.0mm
J100: P4 JP1 - 26 pin IDC; IDC-Header_2x13_P2.54mm_Vertical
J101: C6 service; PinHeader_1x06_P2.54mm_Vertical
J102: QWIIC 3V3 I2C; JST_SH_SM04B-SRSS-TB_1x04-1MP_P1.00mm_Horizontal; LCSC C160404
J103: SHUTTER; JST_XH_B2B-XH-A_1x02_P2.50mm_Vertical
R100, R101, R102, R103: 4.7k; R_0603_1608Metric; LCSC C23162
TP100, TP110: P4_3V3; TestPoint_Pad_D1.5mm
TP101, TP111: P4_5V; TestPoint_Pad_D1.5mm
TP102, TP112: SYNC_MASTER; TestPoint_Pad_D1.5mm
TP103, TP113: CAM_PWR_EN; TestPoint_Pad_D1.5mm
TP104, TP114: SHUTTER_N; TestPoint_Pad_D1.5mm
TP105, TP106, TP115: GND; TestPoint_Pad_D1.5mm
TP107, TP116: FAULT_N; TestPoint_Pad_D1.5mm
TP117: 5V_IN; TestPoint_Pad_D1.5mm

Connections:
5V_IN: TP117.1; also elsewhere on the board
C6_3V3: J100.18 (C6_3V3), J101.2 (C6_3V3)
C6_EN: J100.26 (C6_EN), J101.6 (C6_EN)
C6_IO9: J100.24 (C6_IO9), J101.5 (C6_IO9)
C6_RX: J100.20 (C6_RX), J101.3 (C6_RX)
C6_TX: J100.22 (C6_TX), J101.4 (C6_TX)
CAM_PWR_EN: J100.10 (CAM_PWR_EN), R100.1, TP103.1, TP113.1; also elsewhere on the board
FAULT_N: TP107.1, TP116.1; also elsewhere on the board
GND: C100.2, GL1.1, GL2.1, GL3.1, J100.5 (GND), J100.6 (GND), J100.16 (GND), J101.1 (GND), J102.1 (GND), J103.2 (GND), R100.2, R101.2, TP105.1, TP106.1, TP115.1; also elsewhere on the board
P4_3V3: C100.1, J100.1 (P4_3V3), J100.3 (P4_3V3), J102.2 (P4_3V3), R102.2, R103.2, TP100.1, TP110.1
P4_5V: J100.2 (P4_5V), J100.4 (P4_5V), TP101.1, TP111.1; also elsewhere on the board
P4_RX1: J100.9 (P4_RX1); also elsewhere on the board
P4_RX2: J100.13 (P4_RX2); also elsewhere on the board
P4_RX3: J100.8 (P4_RX3); also elsewhere on the board
P4_RX4: J100.14 (P4_RX4); also elsewhere on the board
P4_SCL: J100.25 (P4_SCL), J102.4 (P4_SCL), R103.1
P4_SDA: J100.23 (P4_SDA), J102.3 (P4_SDA), R102.1
P4_TX1: J100.7 (P4_TX1); also elsewhere on the board
P4_TX2: J100.11 (P4_TX2); also elsewhere on the board
P4_TX3: J100.17 (P4_TX3); also elsewhere on the board
P4_TX4: J100.12 (P4_TX4); also elsewhere on the board
SHUTTER_N: J100.21 (SHUTTER_N), J103.1 (SHUTTER_N), TP104.1, TP114.1
SYNC_MASTER: J100.19 (SYNC_MASTER), R101.1, TP102.1, TP112.1; also elsewhere on the board

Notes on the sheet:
P4 header, controls and I2C
JP1 map measured (board_d4v1.h, ECN-0002/0003). Pin 15 is GPIO35, the P4 boot strap: never connect it. CAM_PWR_EN (GPIO31) enables all four camera switches; R100 holds them off from P4 reset.

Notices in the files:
README.md:
Hardware: CERN-OHL-S-2.0
